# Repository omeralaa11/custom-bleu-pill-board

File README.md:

# Custom Blue Pill Board

This project is a custom-designed version of the popular Blue Pill development board based on the STM32F103C8T6 microcontroller. The design aims to provide a compact, reliable, and easily manufacturable board for embedded systems projects and educational use.

## 🚀 Objective

Redesign the STM32 Blue Pill board to:

- Improve component layout and manufacturability
- Remove unnecessary components for simplicity
- Ensure full compatibility with STM32 development tools and bootloaders

## 📦 Features

- **Microcontroller**: STM32F103C8T6 (ARM Cortex-M3, 72 MHz, 64KB Flash, 20KB RAM)
- **Power Input Options**: USB or external 5V
- **Reset & Boot Buttons**: Onboard tactile switches
- **Debugging**: SWD header for programming and debugging
- **LEDs**: Power and user LEDs for basic feedback
- **Crystal**: 8 MHz external crystal oscillator
- **Compact Form Factor**: Optimized layout for smaller size

## 🛠️ Tools Used

- **EDA Software**: KiCad 9
- **Microcontroller**: STM32F103C8T6
- **Programming**: STM32CubeIDE / STM32CubeProgrammer / PlatformIO

## ✅ Status

- ✅ Schematic Complete
- ✅ PCB Layout Finalized
- ✅ Gerbers Generated
- ⬜️ PCB Assembled and Tested *(Update this once tested)*

## 📌 Future Improvements

- Add reverse-current protection
- Consider support for higher-pin STM32 variants
- Add footprint for optional external Flash/EEPROM

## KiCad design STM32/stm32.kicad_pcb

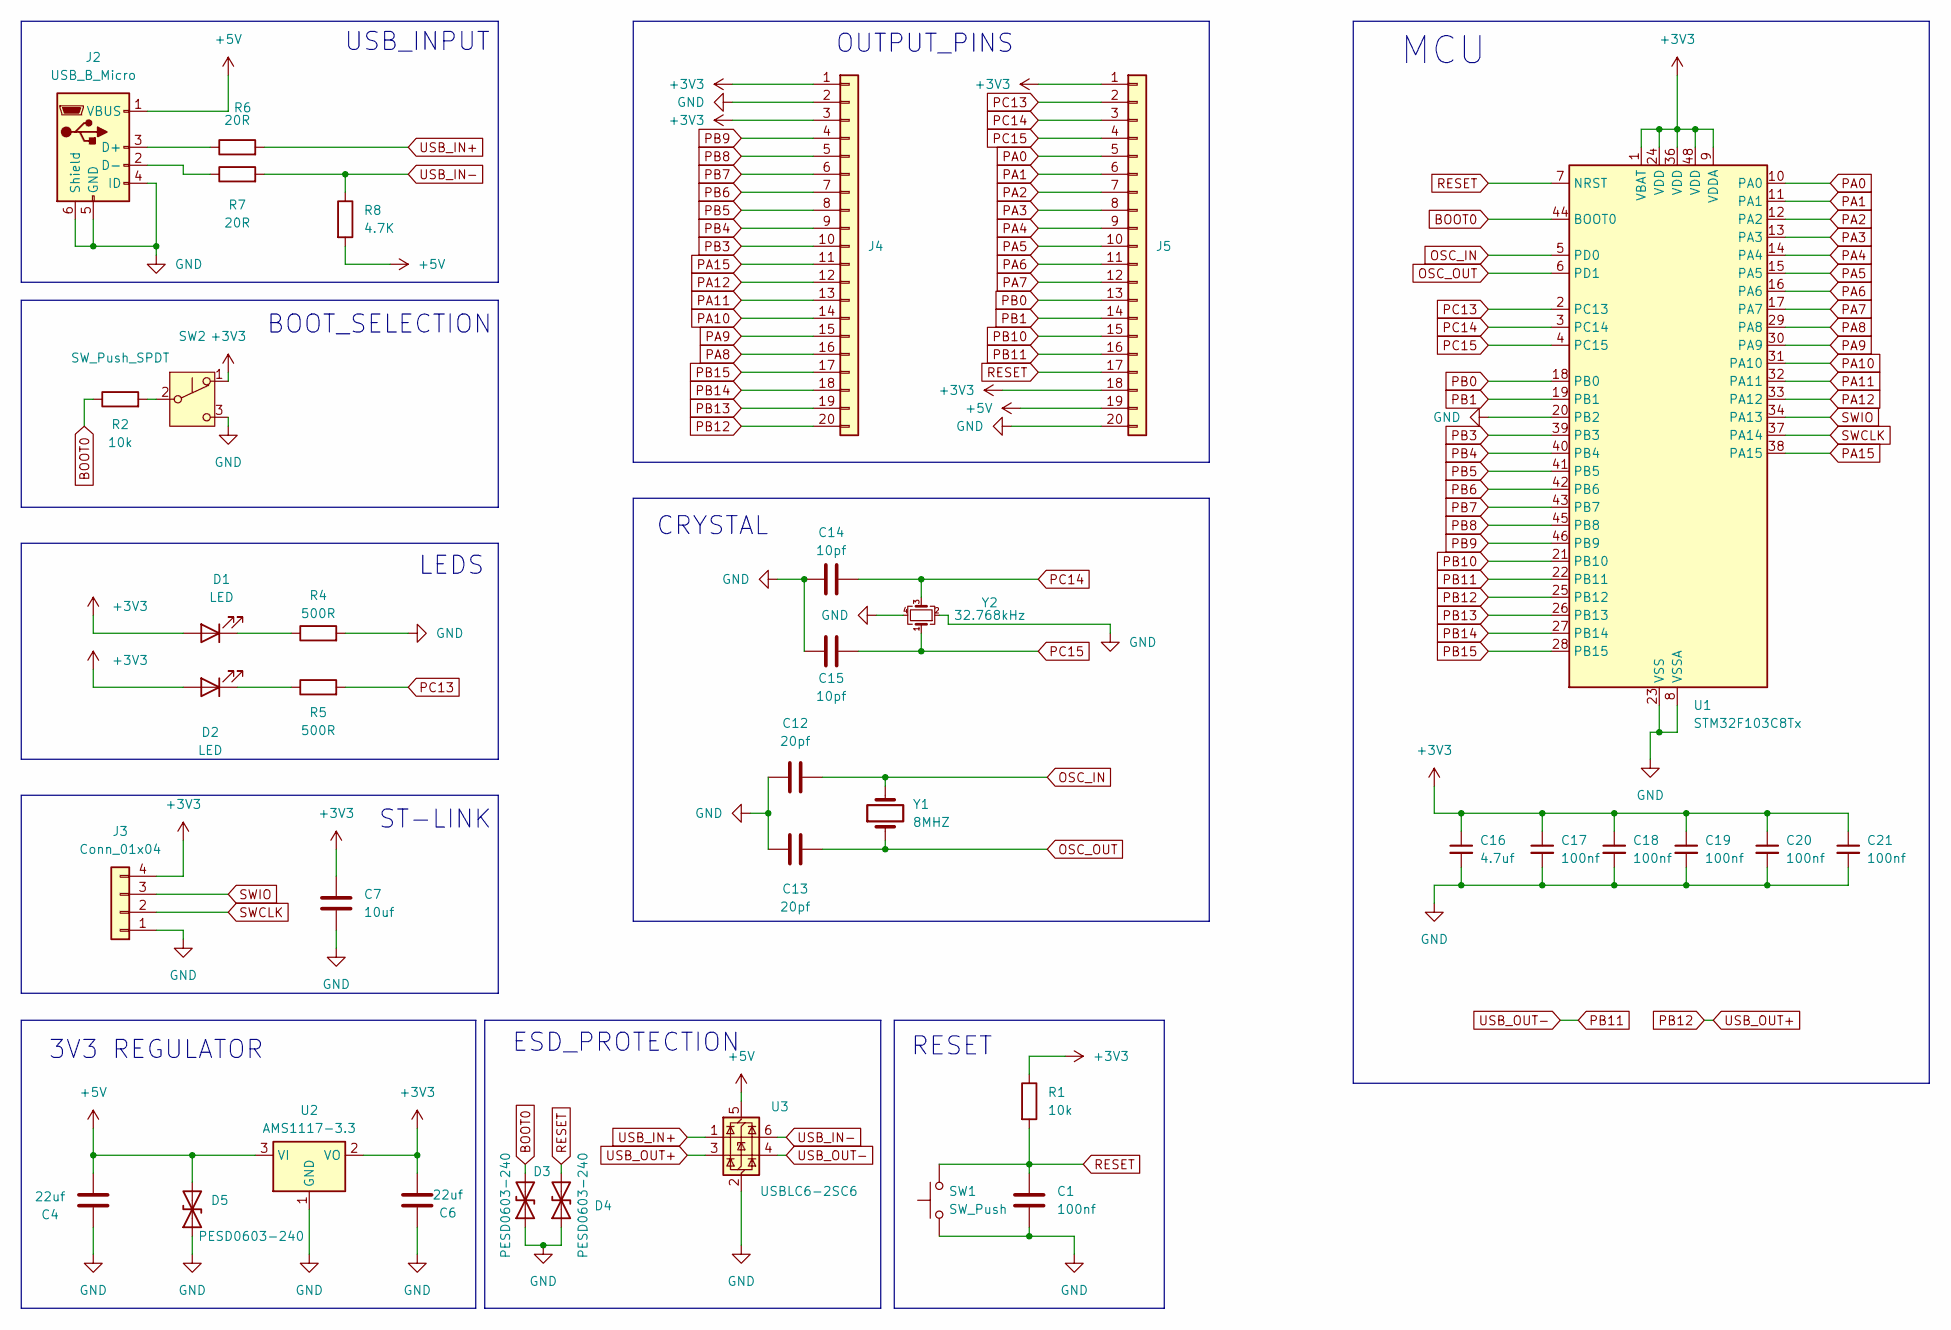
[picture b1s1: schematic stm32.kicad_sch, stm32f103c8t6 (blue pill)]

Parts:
C1, C17, C18, C19, C20, C21: 100nf; C_0201_0603Metric
C4, C6: 22uf; C_0805_2012Metric
C7: 10uf; C_0402_1005Metric
C12, C13: 20pf; C_0201_0603Metric
C14, C15: 10pf; C_0201_0603Metric
C16: 4.7uf; C_0805_2012Metric
D1, D2: LED; LED_0603_1608Metric
D3, D4, D5: PESD0603-240; D_0603_1608Metric
J2: USB_B_Micro; USB_Micro-B_Amphenol_10118193-0001LF_Horizontal
J3: Conn_01x04; PinHeader_1x04_P2.54mm_Horizontal
J4, J5: Conn_01x20; PinHeader_1x20_P2.54mm_Vertical
R1, R2: 10k; R_0402_1005Metric
R4, R5: 500R; R_0603_1608Metric
R6, R7: 20R; R_0603_1608Metric
R8: 4.7K; R_0402_1005Metric
SW1: SW_Push; SW_SPST_CK_RS282G05A3
SW2: SW_Push_SPDT; SW_SPDT_PCM12
U1: STM32F103C8Tx; LQFP-48_7x7mm_P0.5mm
U2: AMS1117-3.3; SOT-223-3_TabPin2
U3: USBLC6-2SC6; SOT-23-6
Y1: 8MHZ; Crystal_SMD_0603-2Pin_6.0x3.5mm
Y2: 32.768kHz; Crystal_SMD_SeikoEpson_FA238-4Pin_3.2x2.5mm

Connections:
+3V3: C6.1, C7.1, C16.1, C17.1, C18.1, C19.1, C20.1, C21.1, D1.2 (A), D2.2 (A), J3.4, J4.1, J4.3, J5.1, J5.18, R1.1, SW2.1 (A), U1.1 (VBAT), U1.9 (VDDA), U1.24 (VDD), U1.36 (VDD), U1.48 (VDD), U2.2 (VO)
+5V: C4.1, D5.2 (A2), J2.1 (VBUS), J5.19, R8.2, U2.3 (VI), U3.5 (VBUS)
BOOT0: D3.2 (A2), R2.1, U1.44 (BOOT0); also elsewhere on the board
GND: C1.2, C4.2, C6.2, C7.2, C12.1, C13.1, C14.1, C15.1, C16.2, C17.2, C18.2, C19.2, C20.2, C21.2, D3.1 (A1), D4.1 (A1), D5.1 (A1), J2.4 (ID), J2.5 (GND), J2.6 (Shield), J3.1, J4.2, J5.20, R4.2, SW1.1, SW2.3 (C), U1.8 (VSSA), U1.20 (PB2), U1.23 (VSS), U1.35 (VSS), U1.47 (VSS), U2.1 (GND), U3.2 (GND), Y2.2, Y2.4
unnamed: D1.1 (K), R4.1
unnamed: D2.1 (K), R5.1
unnamed: J2.3 (D+), R6.1
unnamed: J2.2 (D-), R7.1
unnamed 8: R2.2, SW2.2 (B); also elsewhere on the board
OSC_IN: C12.2, U1.5 (PD0), Y1.2
OSC_OUT: C13.2, U1.6 (PD1), Y1.1
PA0: J5.5, U1.10 (PA0)
PA1: J5.6, U1.11 (PA1)
PA2: J5.7, U1.12 (PA2)
PA3: J5.8, U1.13 (PA3)
PA4: J5.9, U1.14 (PA4)
PA5: J5.10, U1.15 (PA5)
PA6: J5.11, U1.16 (PA6)
PA7: J5.12, U1.17 (PA7)
PA8: J4.16, U1.29 (PA8)
PA9: J4.15, U1.30 (PA9)
PA10: J4.14, U1.31 (PA10)
PA11: J4.13, U1.32 (PA11)
PA12: J4.12, U1.33 (PA12)
PA15: J4.11, U1.38 (PA15)
PB0: J5.13, U1.18 (PB0)
PB1: J5.14, U1.19 (PB1)
PB3: J4.10, U1.39 (PB3)
PB4: J4.9, U1.40 (PB4)
PB5: J4.8, U1.41 (PB5)
PB6: J4.7, U1.42 (PB6)
PB7: J4.6, U1.43 (PB7)
PB8: J4.5, U1.45 (PB8)
PB9: J4.4, U1.46 (PB9)
PB10: J5.15, U1.21 (PB10)
PB11: J5.16, U1.22 (PB11), U3.4 (I/O2)
PB12: J4.20, U1.25 (PB12), U3.3 (I/O2)
PB13: J4.19, U1.26 (PB13)
PB14: J4.18, U1.27 (PB14)
PB15: J4.17, U1.28 (PB15)
PC13: J5.2, R5.2, U1.2 (PC13)
PC14: C14.2, J5.3, U1.3 (PC14), Y2.3
PC15: C15.2, J5.4, U1.4 (PC15), Y2.1
RESET: C1.1, D4.2 (A2), J5.17, R1.2, SW1.2, U1.7 (NRST)
SWCLK: J3.2, U1.37 (PA14)
SWIO: J3.3, U1.34 (PA13)
USB_IN+: R6.2, U3.1 (I/O1)
USB_IN-: R7.2, R8.1, U3.6 (I/O1)

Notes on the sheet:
CRYSTAL
ST-LINK
RESET
ESD_PROTECTION
USB_INPUT
BOOT_SELECTION
MCU
LEDS
OUTPUT_PINS
3V3 REGULATOR

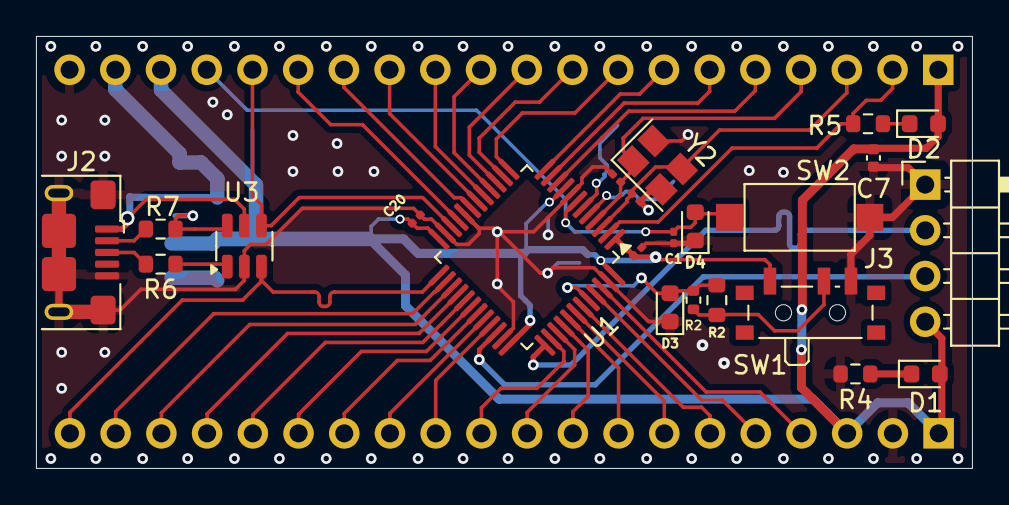
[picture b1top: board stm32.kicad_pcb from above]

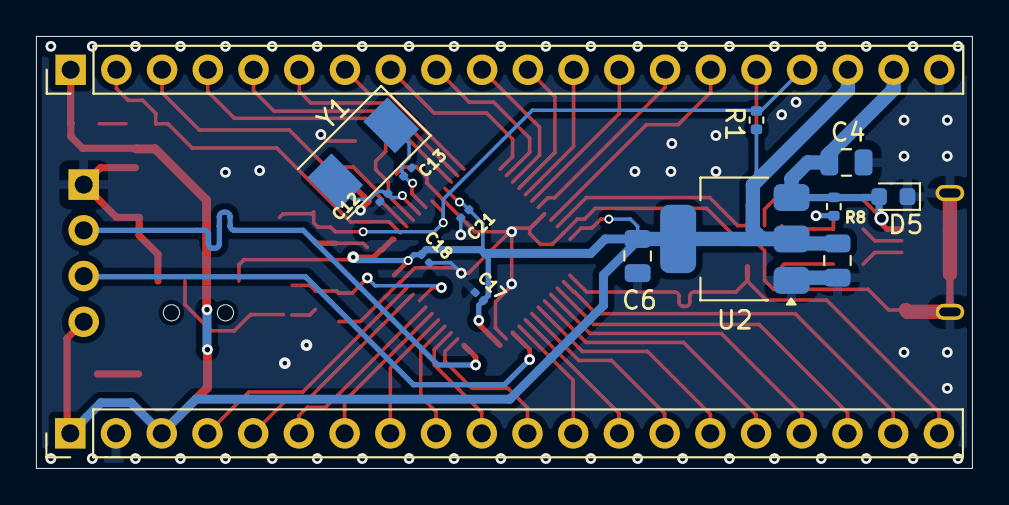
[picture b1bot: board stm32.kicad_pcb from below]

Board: 2 copper layers, 52.0 x 24.0 mm, 38 parts (15 on the bottom side), 48 nets.

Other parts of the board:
R2#2: 10k; R_0402_1005Metric

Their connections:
BOOT0: R2#2.1; also elsewhere on the board
unnamed 8: R2#2.2; also elsewhere on the board

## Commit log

2025-06-15 uploaded the design files
